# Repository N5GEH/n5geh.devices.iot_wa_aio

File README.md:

#   IoT-AIO <br/> Analog IO IoT Wireless Adapter

IoT-AIO is a wireless adapter for developing IoT applications for Industrial and Building Automation Systems based on the Espressif chipset ESP32. The adapter is compatible with:
- current loop signals (0/4-20 mA)
- voltage signals (0/2-10 V)
- passive sensors (RTD, Strain Gauge,..)

The library allows the implemention of IoT applications that rely on MQTT protocol via WiFi/NB-IoT/LTE Cat-M1 interfaces.

## Adapter versions
The Iot-AIO wireless adapter is available in two versions developed using [KiCAD 5.1](https://kicad-pcb.org/) and compatible with:
- [ESP32-PICO-KIT v4](https://docs.espressif.com/projects/esp-idf/en/latest/esp32/hw-reference/esp32/get-started-pico-kit.html) - is an ESP32-based mini development board produced by [Espressif](https://espressif.com/). The board features integrated Wifi and BLE capabilites.
- [FiPy](https://pycom.io/product/fipy/) - is an ESP32-based mini development board produced by [Pycom](https://pycom.io/). The board features integrated Wifi, BLE, LoRa, Sigfox, NB-IoT and LTE Cat-M1

## Development Framework
IoT-AIO relies on the Espressif IoT Development Framework [ESP-IDF](https://github.com/espressif/esp-idf), the official development framework for the [ESP32](https://espressif.com/en/products/hardware/esp32/overview) chip.

The adapter can be easily configured at run-time via a web interface based on HTML forms. The software configurator can be accessed by connecting to the adapter while in AP mode and typing in the browser the IP address `192.168.1.4`. After a succesful change in configuration the wireless adapter will reset. Source code and additional documentation can be found here:
- [AIO Configurator](Firmware/doc/aio_configurator.md)
- [HTML Request Page](Firmware/doc/aio_configurator_request.html)
- [HTML Response Page](Firmware/doc/aio_configurator_response.html)
- [Further Developments](Firmware/doc/developments.md)

## Configuration

### Pinout
IO pinout (top-down):
- 0: GND
- 1: I- amperometric negative pin
- 2: I+ amperometric positive pin
- 3: AO/V- analog output/voltmetric negative pin
- 4: AI/V+ analog output/voltmetric positive pin
- 5: 12 V power supply (use input resistor 120 Ω / 1.5 W for 24 V input)

### Mode
The working mode of the adapter is selected using SW1
- UP: passive mode
    - pin 3 -> V-
    - pin 4 -> V+
- DOWN: analog IO mode
    - pin 3 -> AO
    - pin 4 -> AI

### Input mode
When SW1(DOWN) the input mode of the adapter is selected using SW2
- UP: voltage input mode allows for signals in the range 0 to 10 V
- DOWN: current input mode  allows for signals in the range 0 to 20 mA

### Output mode
When SW1(DOWN) the output mode of the adapter is selected using SW3(1):
- UP: voltage output mode allows for signals in the range 0 to 10 V
- DOWN: current output mode  allows for signals in the range 0 to 20 mA

### Passive mode
When SW1(UP) the output mode of the adapter is selected using SW3(2,3)

| Mode    | SW3(2) | SW3(3) |
|:-------:|:------:|:------:|
| 2-wires |   UP   |   UP   |
| 3-wires |   UP   |  DOWN  |
| 4-wires |  DOWN  |  DOWN  |

### Functions button
The push button BT performs multiple operations depending on the pressure time Tp.

| Pressure Time   |      Action                                                                      |
|:---------------:|:---------------------------------------------------------------------------------|
|     Tp < 1s     | Performs a soft-reset of the adapter                                             |
|1s < Tp < 5s     | Enables the AP mode. If not previously changed, the device will be visible by default with the SSID `ESP_<MAC>`, where <MAC> is the MAC address of the adapter network interface in hex format|
|5s < Tp          | Performs a hard-reset of the adapter deleting the previously stored configuration|

# Publications

We kindly ask academic publications employing based or inspired to IoT-AIO to cite at least one of the following papers:

- M.H. Schraven, C. Guarnieri Calò Carducci, M.A. Baranski, D. Mueller, A. Monti, “Designing a Development Board for Research on IoT Appli-cations in Building Automation Systems,” 36th International Symposiumon  Automation  and  Robotics  in  Construction  (ISARC  2019),  Banff,Canada, 2019, pp. 82-90, [DOI: 10.22260/ISARC2019/0012](https://doi.org/10.22260/ISARC2019/0012)
- C. Guarnieri Calò Carducci, A. Monti, M. H. Schraven, M. Schumacher and D. Mueller, “Enabling ESP32-based IoT Applications in Building Automation Systems,” 2019 II Workshop on Metrology for Industry 4.0 and IoT (MetroInd4.0&IoT), Naples, Italy, 2019, pp. 306-311, [DOI: 10.1109/METROI4.2019.8792852](https://doi.org/10.1109/METROI4.2019.8792852)

# Copyright

2019-2020, Institute for Automation of Complex Power Systems, EONERC  

# License

<br />This work is licensed under a <a rel="license" href="http://creativecommons.org/licenses/by/4.0/">Creative Commons Attribution 4.0 International License</a>.

# Contact

- [Carlo Guarnieri Calò Carducci (PhD)](mailto:cguarnieri@eonerc.rwth-aachen.de)

[Institute for Automation of Complex Power Systems (ACS)](http://www.acs.eonerc.rwth-aachen.de)  
[EON Energy Research Center (EONERC)](http://www.eonerc.rwth-aachen.de)  
[RWTH University Aachen, Germany](http://www.rwth-aachen.de)

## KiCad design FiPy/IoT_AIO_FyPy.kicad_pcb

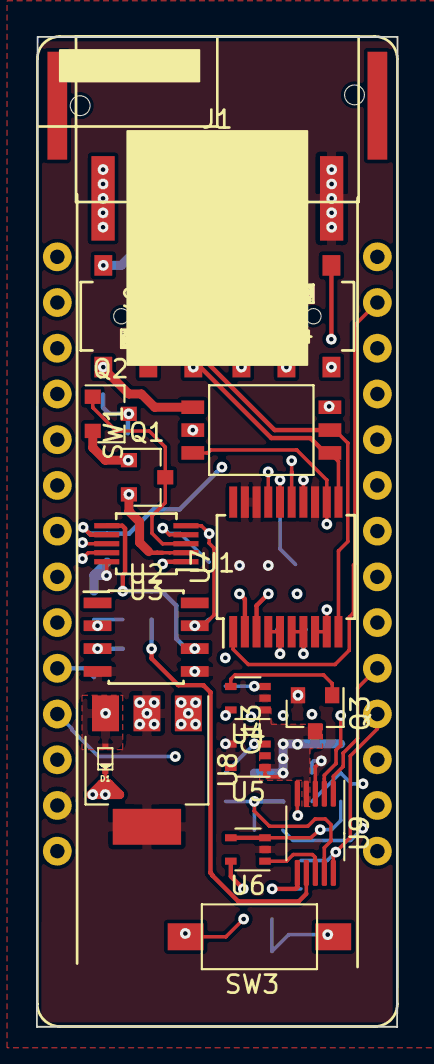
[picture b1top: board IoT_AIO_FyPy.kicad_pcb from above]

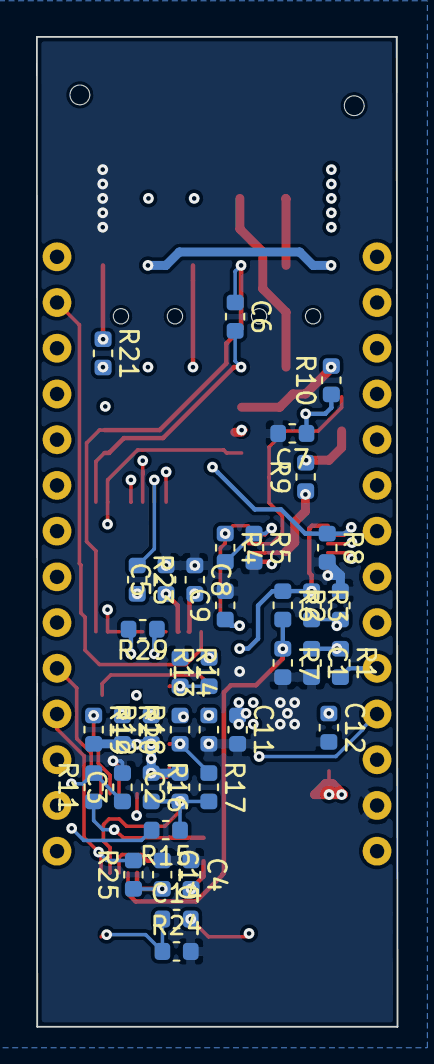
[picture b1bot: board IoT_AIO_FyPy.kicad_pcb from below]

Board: 4 copper layers, 20.0 x 55.0 mm, 57 parts (39 on the bottom side), 52 nets.

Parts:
C1, C3, C6: 1u; C_0603_1608Metric
C2, C4, C5, C8, C9, C10, C12, C13: 100n; C_0603_1608Metric
C7: 10n; C_0603_1608Metric
C11: 220n; C_0603_1608Metric
C14: 100n; R_0603_1608Metric
D1: D_Schottky; BAS52
J1: Conn_01x06; XW4L-06A1-H1
Q1: MMBT5087LT3G; SOT-23
Q2: ISS55EP06LMXTSA1; SOT-23
Q3: SI2302; SOT-23
R1, R11, R24, R25: 10k; R_0603_1608Metric
R2: 4.7k 0.1%; R_0603_1608Metric
R3: 10k 0.1%; R_0603_1608Metric
R4: 22k; R_0603_1608Metric
R5: 8.2k; R_0603_1608Metric
R6, R21: 33k 0.1%; R_0603_1608Metric
R7, R19: 3.3k 0.1%; R_0603_1608Metric
R8: 4990 0.1%; R_0603_1608Metric
R9, R10: 15; R_0603_1608Metric
R12, R14: 3.3k; R_0603_1608Metric
R13: 33k; R_0603_1608Metric
R15: 600 0.1%; R_0603_1608Metric
R16: 1k 0.1%; R_0603_1608Metric
R17: 2.2k 0.1%; R_0603_1608Metric
R18: 500; R_0603_1608Metric
R20: 45.3 0.1%; R_0603_1608Metric
R23: 4.7k; R_0603_1608Metric
R29: 400 0.1%; R_0603_1608Metric
SW1: SW_3PST; 416131160803
SW2: SW_SPDT_x2; AYZ0202AGRL
SW3: SW_Push; PTS636
SW4: SW_DPDT_x2; AYZ0202AGRL
U1: FiPy
U2: TLV07IDR; SOIC-8_3.9x4.9mm_P1.27mm
U3: XTR111AIDGQR; MSOP-10_3x3mm_P0.5mm
U4, U6: TLV333IDCKR; SOT-353_SC-70-5
U5: LM4040DCK-2.0; SOT-353_SC-70-5
U7: MAX31865; SSOP-20_5.3x7.2mm_P0.65mm
U8: LM340MP-5.0/NOPB; SOT-223-3_TabPin2
U9: TMUX1204; VSSOP-10_3x3mm_P0.5mm

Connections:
+3V3: C4.2, C5.1, C8.2, C10.2, C13.2, R12.2, R18.2, R23.2, R25.1, U1.26, U4.5, U6.5, U7.2, U7.3, U9.5, U9.6
+5V: D1.1, U1.28
+24V: C11.1, J1.6, U3.1, U8.1
/ADC_AI: C3.1, R11.2, U1.15
/AI: SW2.1, SW4.5
/AI/AOCAL: R6.2, R7.1, U9.7
/AI/Vcal: C2.1, R15.1, R16.2, R17.2, U9.9
/AO: R10.2, SW1.1, SW2.4
/AO/VREGF: C9.1, R4.1, U2.7, U3.5
/CAL_GPIO: R15.2, U1.10
/CS_SENSOR: R23.1, U1.6, U7.16
/DRDY_SENSOR: U1.13, U7.1
/IFORCE+: J1.3, SW1.3, U7.8, U7.9
/IFORCE-: J1.2, SW1.5, U7.12
/MISO_SENSOR: U1.11, U7.17
/MOSI_SENSOR: U1.12, U7.14
/MUX_A0: U1.5, U9.1
/MUX_A1: R25.2, U1.4, U9.10
/OFFSET_DAC: R13.2, U1.23
/RTDIN+: C6.1, SW1.4, SW2.3, U7.10
/RTDIN-: C6.2, SW1.6, SW2.6, U7.11
/SCK_SENSOR: U1.25, U7.15
/XTR111_EF: U1.18, U3.8
/XTR111_OD: U1.17, U3.9
/XTR111_PWM: R1.2, U1.24
GND: C1.2, C3.2, C4.1, C5.2, C7.2, C8.1, C9.2, C10.1, C11.2, C12.2, C13.1, J1.1, Q3.2, R2.2, R5.2, R7.2, R8.2, R14.1, R24.2, U1.27, U2.4, U3.10, U4.2, U6.2, U7.13, U7.18, U7.19, U8.2, U9.3
GNDA: C2.2, Q3.3, R12.1, R16.1, R19.2, R20.2, U4.1, U5.1, U9.4
unnamed: C1.1, R1.1, U2.3
unnamed: C7.1, Q2.3, R10.1
unnamed: C12.1, D1.2, U8.3
unnamed: C14.1, R24.1, SW3.1
unnamed: C14.2, SW3.2, U1.16
unnamed: J1.4, SW2.5
unnamed: J1.5, SW2.2
unnamed: Q1.1, Q2.2, R9.2
unnamed: Q1.2, R9.1, U3.2
unnamed: Q1.3, Q2.1, U3.3
unnamed: Q3.1, U4.4
unnamed: R2.1, R3.2, U2.2
unnamed: R3.1, R6.1, U2.6, U3.6
unnamed: R4.2, R5.1, U3.4
unnamed: R8.1, SW1.2, U3.7
unnamed: R11.1, U6.3, U6.4
unnamed: R13.1, R14.2, U4.3
unnamed: R17.1, R18.1, U5.3
unnamed: R19.1, SW4.2, U9.2
unnamed: R20.1, SW4.3, SW4.6
unnamed: R21.1, SW4.4
unnamed: R21.2, SW4.1
unnamed: R29.1, U7.4, U7.5
unnamed: R29.2, U7.6, U7.7
unnamed: U6.1, U9.8

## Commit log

2020-06-27 Add README.md
2020-06-27 Project migration
2020-06-27 Firmware migration
2020-06-27 Update README.md, fig/AIO_configurator.png files
2020-07-09 Add LICENSE
